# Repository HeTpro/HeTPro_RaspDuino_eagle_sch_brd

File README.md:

HeTPro_RaspDuino_eagle_sch_brd
==============================

Esquematico y Board del RaspDuino
HeTPro - Herramientas Tecnologicas Profesionales
Guadalajara, Jalisco. 

Diseño creado bajo la licencia CC Creative Commons

Attribution-ShareAlike 4.0 International (CC BY-SA 4.0) 
http://creativecommons.org/licenses/by-sa/4.0/

www.hetpro.com.mx
contacto@hetpro.com.mx

El diseño creado bajo esta licencia es libre de:

Compartir - Compartir y distribuir el material en culquier medio o formato.
Modificar - Adaptar, transformar y reconstruir el material.

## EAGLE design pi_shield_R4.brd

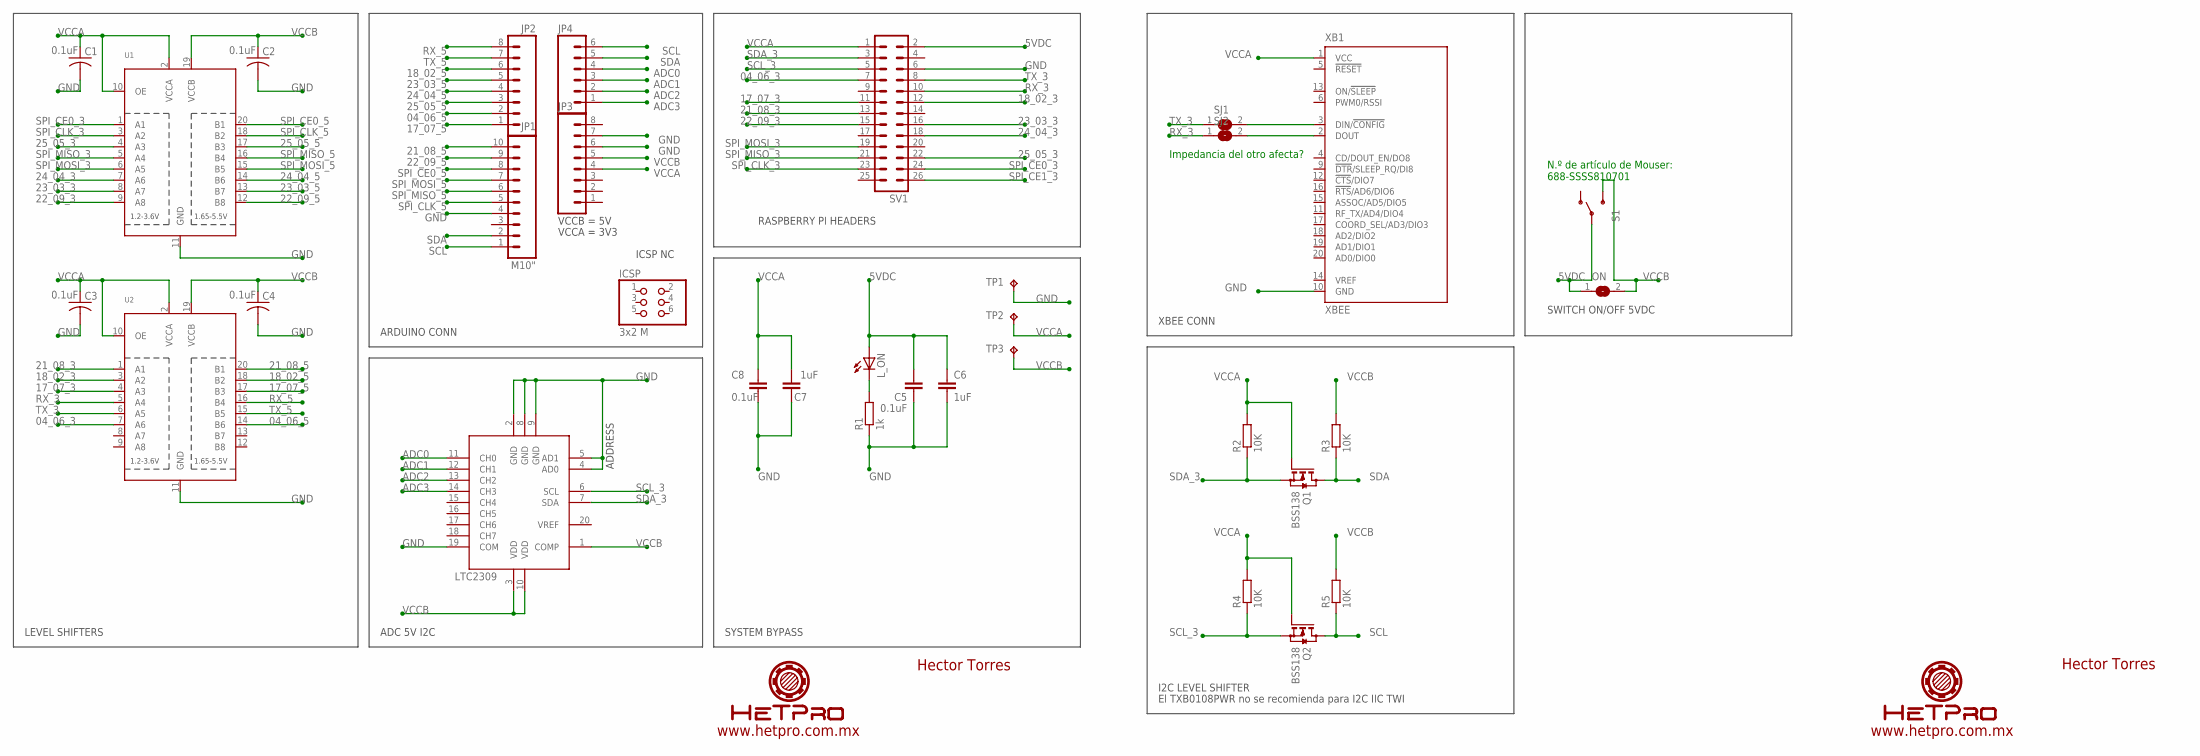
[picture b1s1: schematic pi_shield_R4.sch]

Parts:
C1, C2, C3, C4, C5: 0.1uF; C0603
C6: 1uF; C1206
C7: 1uF; C0603
C8: 0.1uF; C1206
ICSP: 3x2 M; 2X03
JP1: M10"; 1X10
JP2, JP3: M081X08; 1X08
JP4: M06SIP; 1X06
L_ON: LEDCHIPLED_1206; CHIPLED_1206
ON: SJ
Q1, Q2: BSS138; SOT23
R1: 1k; R0603
R2, R3, R4, R5: 10K; R0603
S1: SWITCH-SPST-SMD-A
SJ1, SJ2: SJ
SV1: MA13-2
TP1, TP2, TP3: TPTP20SQ; TP20SQ
U1, U2: TXB0108PWR; TSSOP20
U$4: LTC2309; TSSOP20
XB1: XBEE

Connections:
04_06_3: SV1.7, U2.7 (A6)
04_06_5: JP2.2, U2.14 (B6)
5VDC: C5.2, C6.1, L_ON.A, ON.1, S1.2, SV1.2
17_07_3: SV1.11, U2.4 (A3)
17_07_5: JP2.1, U2.17 (B3)
18_02_3: SV1.12, U2.3 (A2)
18_02_5: JP2.6, U2.18 (B2)
21_08_3: SV1.13, U2.1 (A1)
21_08_5: JP1.10, U2.20 (B1)
22_09_3: SV1.15, U1.9 (A8)
22_09_5: JP1.9, U1.12 (B8)
23_03_3: SV1.16, U1.8 (A7)
23_03_5: JP2.5, U1.13 (B7)
24_04_3: SV1.18, U1.7 (A6)
24_04_5: JP2.4, U1.14 (B6)
25_05_3: SV1.22, U1.4 (A3)
25_05_5: JP2.3, U1.17 (B3)
ADC0: JP4.4, U$4.11 (CH0)
ADC1: JP4.3, U$4.12 (CH1)
ADC2: JP4.2, U$4.13 (CH2)
ADC3: JP4.1, U$4.14 (CH3)
GND: C1.2, C2.2, C3.2, C4.2, C5.1, C6.2, C7.1, C8.2, JP1.4, JP3.6, JP3.7, R1.1, SV1.6, TP1.TP, U1.11 (GND), U2.11 (GND), U$4.2 (GND), U$4.4 (AD0), U$4.5 (AD1), U$4.8 (GND), U$4.9 (GND), U$4.19 (COM), XB1.10 (GND)
unnamed: SJ1.2, XB1.3 (DIN/!CONFIG)
unnamed: SJ2.2, XB1.2 (DOUT)
unnamed: L_ON.C, R1.2
RX_3: SJ2.1, SV1.10, U2.5 (A4)
RX_5: JP2.8, U2.16 (B4)
SCL: JP1.1, JP4.6, Q2.3 (D), R5.1
SCL_3: Q2.2 (S), R4.1, SV1.5, U$4.6 (SCL)
SDA: JP1.2, JP4.5, Q1.3 (D), R3.1
SDA_3: Q1.2 (S), R2.1, SV1.3, U$4.7 (SDA)
SPI_CE0_3: SV1.24, U1.1 (A1)
SPI_CE0_5: JP1.8, U1.20 (B1)
SPI_CE1_3: SV1.26
SPI_CLK_3: SV1.23, U1.3 (A2)
SPI_CLK_5: JP1.5, U1.18 (B2)
SPI_MISO_3: SV1.21, U1.5 (A4)
SPI_MISO_5: JP1.6, U1.16 (B4)
SPI_MOSI_3: SV1.19, U1.6 (A5)
SPI_MOSI_5: JP1.7, U1.15 (B5)
TX_3: SJ1.1, SV1.8, U2.6 (A5)
TX_5: JP2.7, U2.15 (B5)
VCCA: C1.1, C3.1, C7.2, C8.1, JP3.4, Q1.1 (G), Q2.1 (G), R2.2, R4.2, SV1.1, TP2.TP, U1.2 (VCCA), U1.10 (OE), U2.2 (VCCA), U2.10 (OE), XB1.1 (VCC)
VCCB: C2.1, C4.1, JP3.5, ON.2, R3.2, R5.2, S1.3 (S), TP3.TP, U1.19 (VCCB), U2.19 (VCCB), U$4.1 (COMP), U$4.3 (VDD), U$4.10 (VDD)

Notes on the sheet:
Impedancia del otro afecta?
N.º de artículo de Mouser: 688-SSSS810701
ARDUINO CONN
VCCB = 5V
VCCA = 3V3
ICSP NC
LEVEL SHIFTERS
XBEE CONN
I2C LEVEL SHIFTER
El TXB0108PWR no se recomienda para I2C IIC TWI
ADDRESS
SWITCH ON/OFF 5VDC
RASPBERRY PI HEADERS
SYSTEM BYPASS
ADC 5V I2C
www.hetpro.com.mx
Hector Torres

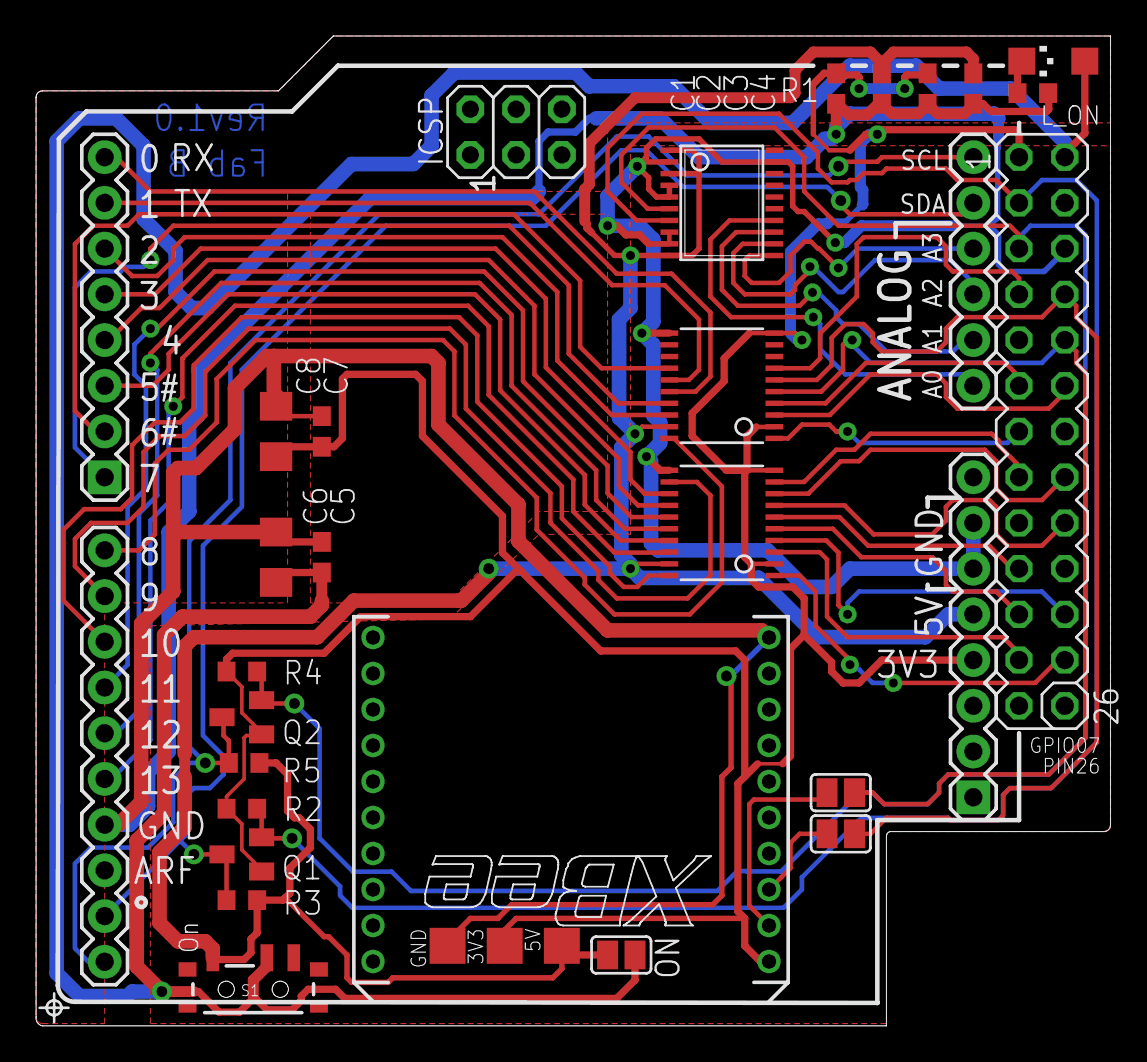
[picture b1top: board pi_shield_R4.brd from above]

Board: 2 copper layers, 59.7 x 55.0 mm, 33 parts (0 on the bottom side), 43 nets.

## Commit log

2014-10-09 :octocat: Added .gitattributes & .gitignore files
2014-10-09 Archivos añadidos
    esquematico y boardfile

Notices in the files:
parts and their libraries:
SparkFun: Licensing: CC v3.0 Share-Alike You are welcome to use this library for commercial purposes.
